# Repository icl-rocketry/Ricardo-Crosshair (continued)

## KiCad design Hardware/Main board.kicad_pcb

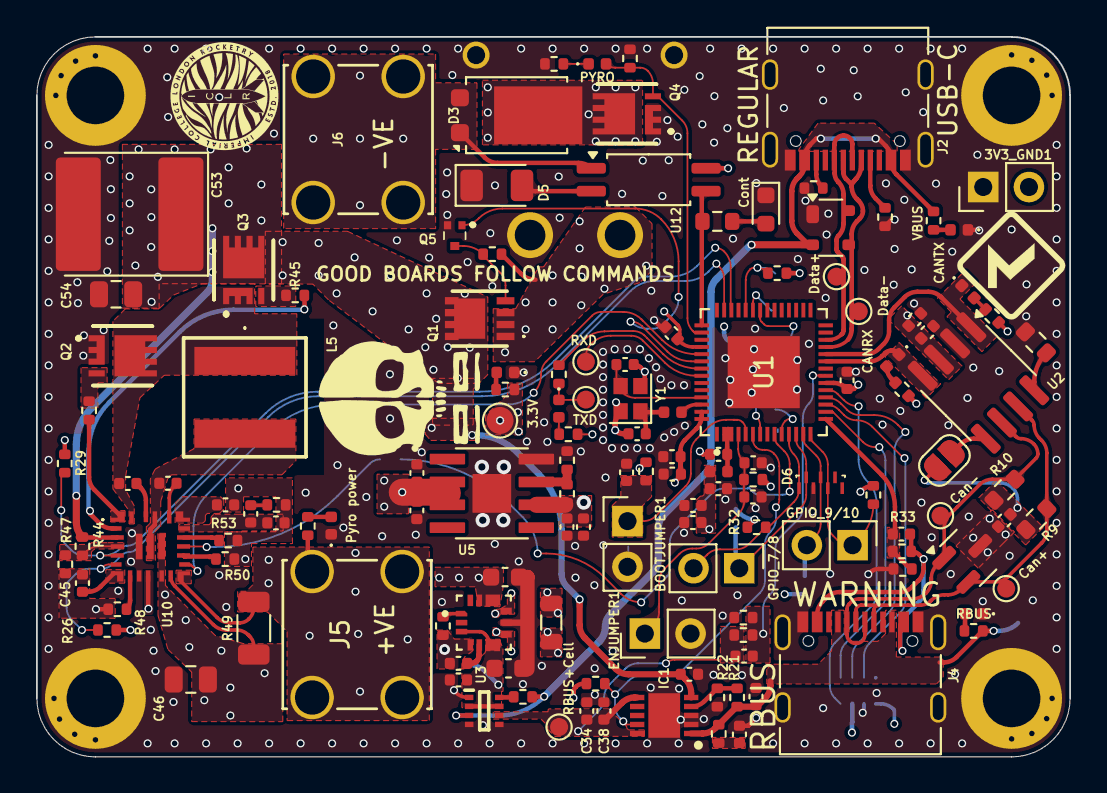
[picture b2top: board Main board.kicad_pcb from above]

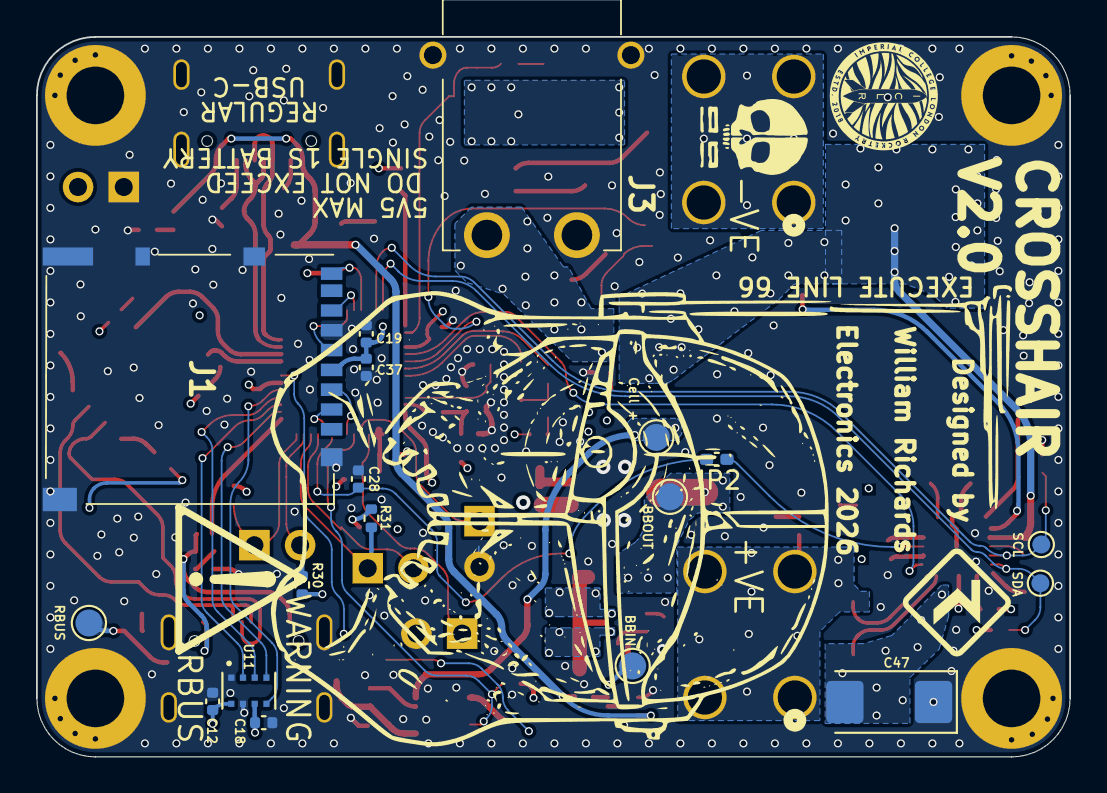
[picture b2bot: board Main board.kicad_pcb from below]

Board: 4 copper layers, 57.4 x 40.0 mm, 157 parts (18 on the bottom side), 93 nets.

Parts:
3V3LED1: BLUE_LED; LED_0402_1005Metric
3V3_GND1: Conn_01x02_Male; PinHeader_1x02_P2.54mm_Vertical
BOOTJUMPER1: Conn_01x02_Male; PinHeader_1x02_P2.54mm_Vertical
C1, C16, C19, C20, C24, C26, C35: 10uF; C_0402_1005Metric
C2, C4, C7, C22, C36, C39: 1uF; C_0402_1005Metric
C3, C5, C6, C8, C10, C11, C27, C28, C37, C51, C52, C56, C57: 0.1uF; C_0402_1005Metric
C9, C45: 10nF; C_0402_1005Metric
C12, C15, C18: 100nF; C_0402_1005Metric
C13, C14: 11pF; C_0402_1005Metric
C17: 47nF; C_0402_1005Metric
C21: 10uF; C_0603_1608Metric
C23: 22uF; C_0603_1608Metric
C25, C50: 4.7uF; C_0402_1005Metric
C34, C38: 22uF; C_0402_1005Metric
C46, C54: 22uF; C_0805_2012Metric
C47: 82uF; CP_EIA-6032-28_Kemet-C
C48: 15pF; C_0402_1005Metric
C49: 1.2nf; C_0402_1005Metric
C53: 180uF; CP_EIA-7260-20_AVX-M
CRXLED1: ORANGE_LED; LED_0402_1005Metric
CTXLED1: GREEN_LED; LED_0402_1005Metric
D1: SM712_SOT23; SOT-23
D2: SP0503BAHT; SOT-143
D3: DST1550S; TO-277B
D4: RED_LED; LED_0603_1608Metric
D5: 954-S-102T; D_1206_3216Metric
D6: RCLAMP3346PQTNT
ENJUMPER1: Conn_01x02_Male; PinHeader_1x02_P2.54mm_Vertical
Firing1: EMERALD_LED; LED_0402_1005Metric
GPIO_7/8, GPIO_9/10: Conn_01x02_Male; PinHeader_1x02_P2.54mm_Vertical
H1, H2, H3, H4: MountingHole_Pad; MountingHole_3.2mm_M3_DIN965_Pad
IC1: LTC4413EDD#PBF; SON50P300X300X80-11N-D
J1: DM3AT-SF-PEJM5_40_; DM3ATSFPEJM540
J2, J4: USB_C_Receptacle_USB2.0; USB_C_Receptacle_Palconn_UTC16-G
J3: XT30PW-M; XT30PWM
J5, J6: 7788; CONN_7788_KEY
JP1: TermJP; SolderJumper-2_P1.3mm_Open_RoundedPad1.0x1.5mm
JP2: CDC; C_0402_1005Metric_Pad0.74x0.62mm_HandSolder
L1: 2.0nH; L_0402_1005Metric
L2: 20nH; L_0402_1005Metric
L3: 1uH; L_0805_2012Metric
L5: PA5432472NLT
LED5: RED_LED; LED_0402_1005Metric
Q1: SISS23DN-T1-GE3; SQS850ENT1_GE3
Q2, Q3, Q4: BSZ025N04LS
Q5: SSM3K15AMFV,L3F; SSM3K15AMFVL3F
R1, R3, R14, R17, R26, R29, R35, R39, R40: 10kΩ; R_0402_1005Metric
R2, R4: 470Ω; R_0402_1005Metric
R5, R18: 1kΩ; R_0402_1005Metric
R6: 499R; R_0402_1005Metric
R7: 3kΩ; R_0402_1005Metric
R8: 0Ω; R_0603_1608Metric
R9, R10: 60Ω; R_0603_1608Metric
R11, R12, R13, R25: 5.1kΩ; R_0402_1005Metric
R15: 14kΩ; R_0402_1005Metric
R16, R53: 56kΩ; R_0402_1005Metric
R19: 120Ω; R_0402_1005Metric
R20: 120Ω; R_0603_1608Metric
R21, R36, R47: 100kΩ; R_0402_1005Metric
R22: 32kΩ; R_0402_1005Metric
R23: 120kΩ; R_0402_1005Metric
R24, R41: 18kΩ; R_0402_1005Metric
R27: 470kΩ; R_0402_1005Metric
R30, R31, R32, R33: 10k; R_0402_1005Metric
R37: 1Ω; R_0402_1005Metric
R44: 178kΩ; R_0402_1005Metric
R45, R46: 10Ω; R_0402_1005Metric
R48: 49.9kΩ; R_0402_1005Metric
R49: 10mΩ; R_1206_3216Metric
R50: 6.19kΩ; R_0402_1005Metric
R52: 160kΩ; R_0402_1005Metric
RBUSLED1: WHITE_LED; LED_0402_1005Metric
TP1, TP2, TP3, TP7, TP9, TP10, TP11, TP12, TP13: TestPoint; TestPoint_Pad_D1.0mm
TP4, TP5, TP6, TP8, TP14: TestPoint; TestPoint_Pad_D1.5mm
TXLED1: GREEN_LED; LED_0402_1005Metric
U1: ESP32-S3; QFN40P700X700X90-57N
U2: SN65HVD230; SOIC-8_3.9x4.9mm_P1.27mm
U3: LM66200DRLR; SOTFL50P160X60-8N
U4: MAX77827AEFD+T; CONV_MAX77827AEFD+T
U5: SC4215ASTRT; SOIC127P599X175-9N
U10: TPS55288QRPMRQ1; TPS552882QRPMRQ1
U11: DPS368; XDCR_DPS310
U12: TCMT1109; SOP-4_4.4x2.6mm_P1.27mm
USBLED1: WHITE_LED; LED_0402_1005Metric
Y1: R940000171; Crystal_SMD_2016-4Pin_2.0x1.6mm

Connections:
+3V3: 3V3_GND1.2, C1.1, C4.1, C5.1, C7.1, C9.1, C10.1, C11.1, C12.1, C15.1, C16.1, C18.1, C19.1, C26.2, C27.2, C37.1, J1.4 (VDD), L1.1, R1.1, R2.1, R3.1, R4.2, R5.1, R16.1, R18.1, R26.1, R27.1, R29.1, R30.1, R31.1, R32.1, R33.1, R35.1, TP6.1, U1.20 (VDD3P3_RTC), U1.46 (VDD3P3_CPU), U1.55 (VDDA), U1.56 (VDDA), U2.3 (VCC), U5.6 (VOUT), U11.6 (VDDIO), U11.8 (VDD), U12.4
+16.8V: C57.1, J4.A4 (VBUS), J4.A9 (VBUS), J4.B4 (VBUS), J4.B9 (VBUS), R23.1
/BOOT: BOOTJUMPER1.1, C8.1, R3.2, U1.5 (GPIO0/BOOT)
/BatteryV_LOG: C56.2, R40.2, R41.1, U1.21 (GPIO15/ADC2_CH4/XTAL_32K_P)
/BuckBoost_INT: U1.47 (MTDI/JTAG/GPIO41), U10.14 (FB/~INT)
/CAN+: D1.2 (A2), J4.A6 (D+), J4.B6 (D+), R9.1, TP7.1, U2.7 (CANH)
/CAN-: D1.1 (A1), J4.A7 (D-), J4.B7 (D-), R10.2, TP3.1, U2.6 (CANL)
/CAN-BUS/Vref: JP1.1 (A), U2.5 (Vref)
/CAN_RX: CRXLED1.1 (K), U1.23 (GPIO17/ADC2_CH6/DAC_2), U2.4 (R)
/CAN_TX: CTXLED1.1 (K), U1.24 (GPIO18/ADC2_CH7/DAC_1), U2.1 (D)
/CHIP_PU: C2.1, C3.1, ENJUMPER1.1, R1.2, U1.4 (CHIP_PU/RESET)
/CS_Baro: U1.17 (GPIO12/ADC2_CH1), U11.2 (~CSB)
/Cell-switch: Q5.1 (G), U1.48 (MTMS/JTAG/GPIO42)
/Cont 1: R20.1, U1.43 (GPIO38), U12.3
/Current_sens: C28.2, JP2.2 (B), U1.9 (GPIO4/ADC1_CH3)
/Data+: D2.4 (K), J2.A6 (D+), J2.B6 (D+), TP2.1, U1.26 (GPIO20/USB_D+/ADC2_CH9)
/Data-: D2.3 (K), J2.A7 (D-), J2.B7 (D-), TP1.1, U1.25 (GPIO19/USB_D-/ADC2_CH8)
/DeployV_LOG: C57.2, R23.2, R24.1, U1.15 (GPIO10/ADC1_CH9)
/GPIO7: D6.1 (K/A_1), GPIO_7/8.2, R32.2, U1.11 (GPIO6/ADC1_CH5)
/GPIO8: D6.5 (K/A_4), GPIO_7/8.1, R31.2, U1.12 (GPIO7/ADC1_CH6)
/GPIO9: D6.6 (K/A_5), GPIO_9/10.2, R30.2, U1.13 (GPIO8/ADC1_CH7)
/GPIO10: D6.3 (K/A_2), GPIO_9/10.1, R33.2, U1.14 (GPIO9/ADC1_CH8)
/ID_Stat: IC1.9 (STAT), R27.2, U1.6 (GPIO1/ADC1_CH0)
/MISO_Baro: U1.19 (GPIO14/ADC2_CH3), U11.5 (SDO)
/MOSI_Baro: U1.18 (GPIO13/ADC2_CH2), U11.3 (SDI)
/Nuke 1: Firing1.2 (A), Q4.4 (G), R39.1, U1.44 (MTCK/JTAG/GPIO39)
/Power/BBIN: C20.1, C21.1, TP4.1, U3.2 (VOUT_1), U3.7 (VOUT_2), U4.3 (EN), U4.6 (IN)
/Power/BBOUT: C23.1, C24.1, C25.1, TP8.1, U4.11 (OUT), U4.13 (OUTS), U5.2 (EN), U5.3 (VIN)
/Power/BIAS: C22.1, U4.5 (BIAS)
/Power/Cell+_gate: Q1.4 (G), Q5.3 (D), R36.1
/Power/FBIn: R16.2, R17.1, U5.7 (ADJ)
/Power/LX1: L3.1, U4.8 (LX1)
/Power/LX2: L3.2, U4.10 (LX2)
/Power/RBUS + Cell: C34.1, C38.1, C56.1, IC1.6 (OUTB), IC1.10 (OUTA), R40.1, TP13.1, U3.6 (VIN2)
/Power/SEL: R15.1, U4.1 (SEL)
/Pyro/PYRO-ve: D3.1 (A), D3.2 (A), J6.1, J6.2, J6.3, J6.4, U12.1
/PyroPWR: J5.1, J5.2, J5.3, J5.4, R7.1, R49.2, U10.13 (ISN_1), U10.29 (ISN_2)
/RXD: TP10.1, U1.50 (U0RXD/PROG/GPIO44)
/SCK_Baro: U1.16 (GPIO11/ADC2_CH0), U11.4 (SCK)
/SCL_I2C: R29.2, TP11.1, U1.40 (GPIO35), U10.5 (SCL)
/SDA_I2C: R26.2, TP12.1, U1.41 (GPIO36), U10.6 (SDA)
/SD_CLK: J1.5 (CLK), U1.36 (SPICLK_N/GPIO48)
/SD_CMD: J1.3 (CMD), U1.7 (GPIO2/ADC1_CH1)
/SD_DAT0: J1.7 (DAT0), U1.37 (SPICLK_P/GPIO47)
/SD_DAT3: J1.2 (CD/DAT3), U1.10 (GPIO5/ADC1_CH4)
/SD_DET: J1.CD1 (CARD_DETECT), R35.2, U1.38 (GPIO33)
/TXD: R6.1, TP9.1, TXLED1.1 (K)
/Voltage Regulation/CDC: JP2.1 (A), U10.16 (CDC)
/Voltage Regulation/DITH/SYNC_2: C45.1, U10.7 (DITH/SYNC_1), U10.28 (DITH/SYNC_2)
/Voltage Regulation/DR1L_2: R46.2, U10.1 (DR1L_1), U10.27 (DR1L_2)
/Voltage Regulation/ISP: C46.1, C47.2, R49.1, U10.11 (VOUT_1), U10.12 (ISP), U10.26 (VOUT_2)
/Voltage Regulation/SW2_2: C52.2, L5.2, U10.21 (SW2_1), U10.25 (SW2_2)
/Voltage Regulation/VCC_2: C50.2, U10.19 (VCC_1), U10.30 (VCC_2)
Cell_+: C36.1, C53.1, C54.2, IC1.5 (INB), Q1.5 (D_1), Q1.6 (D_2), Q1.7 (D_3), Q1.8 (D_4), Q1.9 (D_5), Q1.10 (D_6), Q1.11 (D_7), Q3.5 (D), Q3.6 (D), Q3.7 (D), Q3.8 (D), Q3.A5 (D), R44.1, TP14.1, U10.3 (VIN)
Cell_Out: J3.1 (+), Q1.1 (S_1), Q1.2 (S_2), Q1.3 (S_3), R36.2
GND: 3V3LED1.1 (K), 3V3_GND1.1, BOOTJUMPER1.2, C1.2, C2.2, C3.2, C4.2, C5.2, C6.2, C7.2, C8.2, C9.2, C10.2, C11.2, C12.2, C13.2, C14.2, C15.2, C16.2, C17.2, C18.2, C19.2, C20.2, C21.2, C22.2, C23.2, C24.2, C25.2, C26.1, C27.1, C28.1, C34.2, C35.2, C36.2, C37.2, C38.2, C39.2, C45.2, C46.2, C47.1, C48.1, C50.1, C53.2, C54.1, D1.3 (common), D2.1 (A), D4.1 (K), D5.1 (K), D6.2 (GND), ENJUMPER1.2, H1.1, H2.1, H3.1, H4.1, IC1.2 (ENBA), IC1.3 (GND_1), IC1.11 (GND_2), J1.6 (VSS), J1.MP1, J1.MP2, J1.MP3, J1.MP4, J1.MP5, J2.A1 (GND), J2.A12 (GND), J2.B1 (GND), J2.B12 (GND), J2.S1 (SHIELD), J3.2 (-), J3.3 (MP), J3.4 (MP), J4.A1 (GND), J4.A12 (GND), J4.B1 (GND), J4.B12 (GND), J4.S1 (SHIELD), LED5.1 (K), Q2.1 (S), Q2.2 (S), Q2.3 (S), Q2.A1 (S), Q4.1 (S), Q4.2 (S), Q4.3 (S), Q4.A1 (S), Q5.2 (S), R8.2, R11.2, R12.1, R15.2, R17.2, R19.2, R22.2, R24.2, R39.2, R41.2, R47.2, R48.2, R50.2, R52.1, R53.1, RBUSLED1.1 (K), U1.57 (GND), U2.2 (GND), U3.1 (GND_1), U3.4 (~ON), U3.5 (GND_2), U4.4 (AGND), U4.9 (PGND), U5.8 (GND), U5.9 (GND), U10.9 (PGND_1), U10.10 (AGND), U10.24 (PGND_2), U11.1 (GND), U11.7 (GND), USBLED1.1 (K), Y1.2, Y1.4
unnamed: 3V3LED1.2 (A), R4.1
unnamed: C6.1, L1.2, U1.2 (VDD3P3), U1.3 (VDD3P3)
unnamed: C14.1, L2.2, Y1.1
unnamed: C35.1, R37.2
unnamed: C49.1, R52.2
unnamed: CRXLED1.2 (A), R18.2
unnamed: CTXLED1.2 (A), R5.2
unnamed: D3.3 (K), Q4.5 (D), Q4.6 (D), Q4.7 (D), Q4.8 (D), Q4.A5 (D)
unnamed: D4.2 (A), R20.2
unnamed: D5.2 (A), U12.2
unnamed: Firing1.1 (K), R19.1
unnamed: IC1.4 (ENBB), R21.2, R22.1
unnamed: J2.A5 (CC1), R11.1
unnamed: J2.B5 (CC2), R12.2
unnamed: C17.1, JP1.2 (B), R9.2, R10.1
unnamed: LED5.2 (A), R7.2
unnamed: Q2.4 (G), R46.1
unnamed: Q3.4 (G), R45.1
unnamed: R25.2, RBUSLED1.2 (A)
unnamed: R2.2, TXLED1.2 (A)
unnamed: R6.2, U1.49 (U0TXD/PROG/GPIO43)
unnamed: C13.1, U1.53 (XTAL_N), Y1.3
unnamed: L2.1, U1.54 (XTAL_P)
unnamed: R8.1, U2.8 (Rs)
unnamed: R14.2, U3.8 (ST)
unnamed: C51.2, U10.22 (BOOT1)
unnamed: C52.1, U10.20 (BOOT2)
unnamed: C48.2, C49.2, U10.18 (COMP)
unnamed: R45.2, U10.2 (DR1H)
unnamed: R44.2, R47.1, U10.4 (EN/UVLO)
unnamed: R48.1, U10.8 (FSW)
unnamed: R53.2, U10.17 (ILIM)
unnamed: R50.1, U10.15 (MODE)
unnamed: C51.1, L5.1, Q2.5 (D), Q2.6 (D), Q2.7 (D), Q2.8 (D), Q2.A5 (D), Q3.1 (S), Q3.2 (S), Q3.3 (S), Q3.A1 (S), U10.23 (SW1)
unnamed: R13.2, USBLED1.2 (A)
RBUS_uC_V: C39.1, IC1.1 (INA), J4.A5 (CC1), J4.B5 (CC2), R21.1, R25.1, R37.1, TP5.1
VBUS: D2.2 (K), J2.A4 (VBUS), J2.A9 (VBUS), J2.B4 (VBUS), J2.B9 (VBUS), R13.1, R14.1, U3.3 (VIN1)

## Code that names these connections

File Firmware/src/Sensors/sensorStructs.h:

#pragma once
/*
Baro, INA current sense, and ADC sense to help with separation
*/

#include <cstdint>

namespace SensorStructs
{
    struct BARO_t
    {
        float alt;   // altitude 
        float temp;  // temperature 
        float press; // pressure 
    };

    struct ADC_V_RAIL_t
    {
        int volt;    // Voltage in mV
        int percent; // Percentage in reference to max voltage expeceted
    };

    struct INA_V_RAIL_t
    {
        int volt;    // Voltage in mV
        int current; // Current in mA
        int power;   // Power in mW
        int percent; // Percentage in reference to max voltage expeceted
    };

    struct STATE_t
    {
        // ADC GPIO monitoring
        ADC_V_RAIL_t BatteryV_LOG; // GPIO15
        ADC_V_RAIL_t DeployV_LOG;  // GPIO10

        // Barometer sensor
        BARO_t baro;

        // INA219 current sensor for pyro
        INA_V_RAIL_t deprail;
    };
}

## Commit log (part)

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2024-11-16 Main + subsection PCB
    Created files to work on individually
2024-11-16 Change folder structure
2024-11-19 Sensor completed
    Barometer circuit done.
2024-11-19 Added pyro circuit
2024-12-07 Removed unused 'Main board' file
2024-12-07 Barometer sensor SPI
2025-01-21 Barometer fix + Photo sensor
    Fixed orientation of ground for barometer. Added Photo sensor + photo sensor symbol in library.
    Need to determine resistance for photo sensor circuit.
2025-01-28 USB-C + Voltage stuff
2025-02-08 Voltage regulation done + used photo ic sensor library
2025-02-08 Added some pins
2025-02-16 New Buck boost converter
    + new sorted circuit, voltage regulation not finalised
2025-03-01 PCB mid design
2025-03-03 PCB done more ish
2025-03-07 Crosshair V1.0
    New pyro connectors, silkscreen sorted, mostly connected properly + cool new name and image
2025-03-08 SD card fix + logos
    Changed SD card from the lock in to the push in
2025-03-18 Swapped battery & nichrome positions
    fixed crystal and other small things
2025-03-21 Applied more review suggestions
2025-03-22 Testpoints + footprints + AGND plane
2025-04-01 Added MOSFET circuit to turn cell power on/off
2025-04-01 Test point + Net shape change
2025-05-06 Crosshair post review 2
    Layout redesign + changes implemented. Traces not yet complete
2025-05-06 Traces connected + rejigging
    Most DRC errors taken care of
2025-05-07 Added extra vias
2025-05-13 Changed fill
2025-05-18 Major changes made to layout
2025-05-31 I2C 'bus' sorted
2025-05-31 Removed voids
2025-05-31 Added vias
2025-06-03 Remove more voids
2025-06-07 Final before buck boost converter moved
2025-06-07 New-ish layout with moved buck boost converter
2025-06-07 Saved changes
2025-06-07 Did some work on the silkscreen
2025-06-26 GPIO broken out + post review 4
2025-06-26 Extra tweaks - current sense etc
2025-06-26 Silkscreen for gpio breakout
2025-06-30 Changed mosfet + added top plane for Cell_+ and fixed silkscreen
2025-07-01 Changed buck boost inductor + changed planes and vias
2025-07-03 Started on Firmware
    Copied over the defined states from Greg
2025-07-07 Submodules added
2025-07-08 Added voltage ref for post ideal diode
    (more firmware too)
2025-07-22 Moved a 3V3 decoupling capacitor for ESP32
2025-07-31 Mega commit
    Post review changes
2025-07-31 Silkscreen label
    Made sure PCB file was saved before push...
2025-10-02 Big Firmware push
2025-10-03 Big changes
2025-10-06 States refresh + logic
    New states, removed un needed ones + passing in correct information into each one + pyro/default system implemented
    Need to sort pyro deployment logic
2025-10-06 Pyro logic should be sorted
2025-10-06 Fixed typo in pyro logic
2025-10-09 SRC changes
2025-11-11 Version 1: complete
    Firmware fixed by Riley at EuRoC
2025-12-19 fix: Fix subcomponent weirdness?
2025-12-19 feat: Some minor software things
2026-01-23 V2 hardware changes
    - Removed current sensor IC
    - Removed photo sensor IC
2026-02-07 Firmware push
    - started library for TPS55288
2026-02-17 Small hardware V2 changes
2026-05-13 V2 changes, PCB finished
2026-05-18 V2 changes, post review work
2026-05-18 More V2 changes
2026-05-20 Board touch ups
2026-05-27 More V2 changes
    Mainly changed to use Ω symbol for resistors. Fixed the CDC pin for the buck boost
2026-06-06 Post second Jack review
    Adopted most changes
2026-06-06 Silkscreen fix
2026-06-18 Feat: Added more vias + changed silkscreen
2026-06-23 Ready to order
2026-06-24 reformatted and renamed file
2026-06-24 changed 1 footprint
